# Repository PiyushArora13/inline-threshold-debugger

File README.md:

# inline-threshold-debugger

Non-Intrusive USB-C Inline Diagnostic PCB for Master–Slave Systems

# Overview

This project presents a non-intrusive inline hardware debugger PCB designed for master–slave embedded architectures, where continuous electrical monitoring is required without altering normal system behavior. The board is placed directly in-line between master and slave nodes, enabling real-time observation of voltage and current characteristics while preserving signal integrity.

The design focuses on high-impedance sensing and comparator-based threshold detection, ensuring that monitored signals experience minimal loading and no functional disturbance. This approach allows the debugger to operate transparently within active systems, making it suitable for live diagnostics, validation, and safety monitoring.

A USB Type-C pass-through interface is used for both input and output, providing a compact, reversible, and standardized physical layer compatible with modern embedded and robotics platforms.

# System Architecture

The PCB is built around an Arduino Nano (ATmega328P), which serves as the central processing unit for data acquisition, threshold evaluation, and status indication. The microcontroller samples analog signals via its ADC and coordinates with dedicated comparator stages to classify operating conditions deterministically.

Current sensing is implemented using the ACS712 Hall-effect current sensor, providing galvanically isolated measurement with low insertion impact on the monitored path. This enables accurate current monitoring while maintaining electrical separation and system safety.

Voltage monitoring is achieved through a high-impedance sensing network followed by comparator stages configured with predefined threshold levels. Comparator outputs allow fast detection of limit violations independent of firmware execution latency, ensuring reliable indication under transient conditions.

The inline signal path is designed to maintain impedance continuity between master and slave devices, allowing the debugger PCB to function as a transparent diagnostic layer rather than an active system element.

# Threshold Evaluation and Visual Indication

Measured voltage and current parameters are continuously evaluated against predefined threshold regions. The system provides immediate visual feedback through:

Discrete LEDs indicating individual threshold events

An RGB LED representing overall system state:

Green – Normal / safe operating region

Yellow – Warning or near-limit condition

Red – Critical or unsafe operating condition

This hardware-level indication enables rapid fault identification without requiring external instruments or software-based debugging tools.

# Design Intent and Rationale

Non-intrusive monitoring: High-impedance sensing and isolated current measurement prevent disturbance of the original signal path.

Comparator-based thresholding: Ensures fast, deterministic response independent of microcontroller timing.

Inline architecture: Allows real-time diagnostics in active master–slave systems.

USB Type-C interface: Provides a compact, reversible, and standardized physical connection.

Separation of sensing and indication: Improves robustness and simplifies system-level fault analysis.

# Applications

Inline debugging of master–slave embedded systems

Power and signal integrity validation

Current and voltage health monitoring

Safety threshold enforcement in robotics and control systems

Rapid fault detection during system integration and testing

Project Status

Hardware: Prototype PCB designed and validated

Firmware: Threshold evaluation and visual indication logic implemented

Future work: Data logging, configurable thresholds, and host-side visualization

# Note on File Viewing

KiCad design files are stored in source format and are not rendered by GitHub. Please clone or download the repository and open it in KiCad to view schematics and PCB layouts. Rendered images are included for reference

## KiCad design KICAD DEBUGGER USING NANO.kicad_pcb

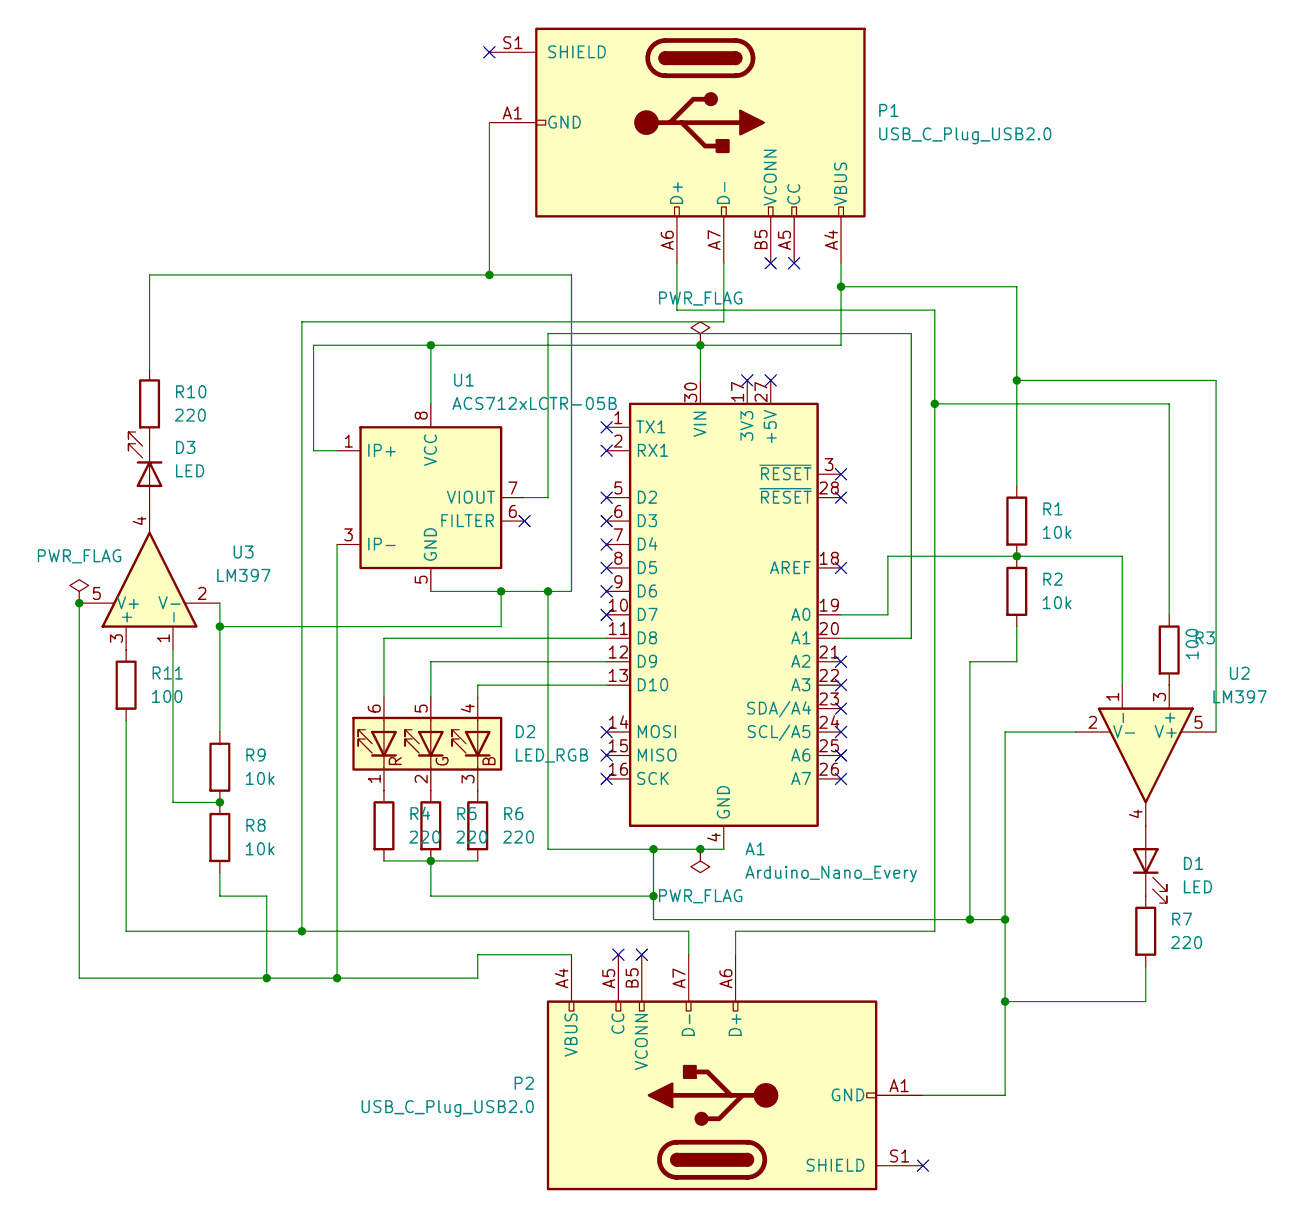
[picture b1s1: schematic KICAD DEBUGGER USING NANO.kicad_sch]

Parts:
A1: Arduino_Nano_Every; Arduino_Nano
D1, D3: LED; LED_0201_0603Metric
D2: LED_RGB; LED_RGB_5050-6
P1, P2: USB_C_Plug_USB2.0; USB_C_Receptacle_GCT_USB4085
R1, R2, R8, R9: 10k; R_2512_6332Metric
R3, R11: 100; R_2512_6332Metric
R4, R5, R6, R7, R10: 220; R_2512_6332Metric
U1: ACS712xLCTR-05B; SOIC-8_3.9x4.9mm_P1.27mm
U2, U3: LM397; SOT-23-5

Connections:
unnamed: A1.19 (A0), R1.2, R2.1, U2.1 (-)
unnamed: A1.20 (A1), U1.7 (VIOUT)
unnamed: A1.11 (D8), D2.6 (RA)
unnamed: A1.12 (D9), D2.5 (GA)
unnamed: A1.13 (D10), D2.4 (BA)
unnamed 5: A1.30 (VIN), P1.A4 (VBUS), P1.A9 (VBUS), P1.B4 (VBUS), P1.B9 (VBUS), R1.1, U1.1 (IP+), U1.2 (IP+), U1.8 (VCC), U2.5 (V+); also elsewhere on the board
unnamed: D1.2 (A), U2.4
unnamed: D1.1 (K), R7.1
unnamed: D2.3 (BK), R6.1
unnamed: D2.2 (GK), R5.1
unnamed: D2.1 (RK), R4.1
unnamed: D3.2 (A), U3.4
unnamed: D3.1 (K), R10.2
unnamed 13: P1.A6 (D+), P2.A6 (D+), R3.1; also elsewhere on the board
unnamed 14: P1.A7 (D-), P2.A7 (D-), R11.2; also elsewhere on the board
unnamed 15: A1.4 (GND), A1.29 (GND), P1.A1 (GND), P1.A12 (GND), P1.B1 (GND), P1.B12 (GND), P2.A1 (GND), P2.A12 (GND), P2.B1 (GND), P2.B12 (GND), R2.2, R4.2, R5.2, R6.2, R7.2, R9.1, R10.1, U1.5 (GND), U2.2 (V-), U3.2 (V-); also elsewhere on the board
unnamed: R3.2, U2.3 (+)
unnamed: R11.1, U3.3 (+)
unnamed: R8.1, R9.2, U3.1 (-)
unnamed 19: P2.A4 (VBUS), P2.A9 (VBUS), P2.B4 (VBUS), P2.B9 (VBUS), R8.2, U1.3 (IP-), U1.4 (IP-), U3.5 (V+); also elsewhere on the board

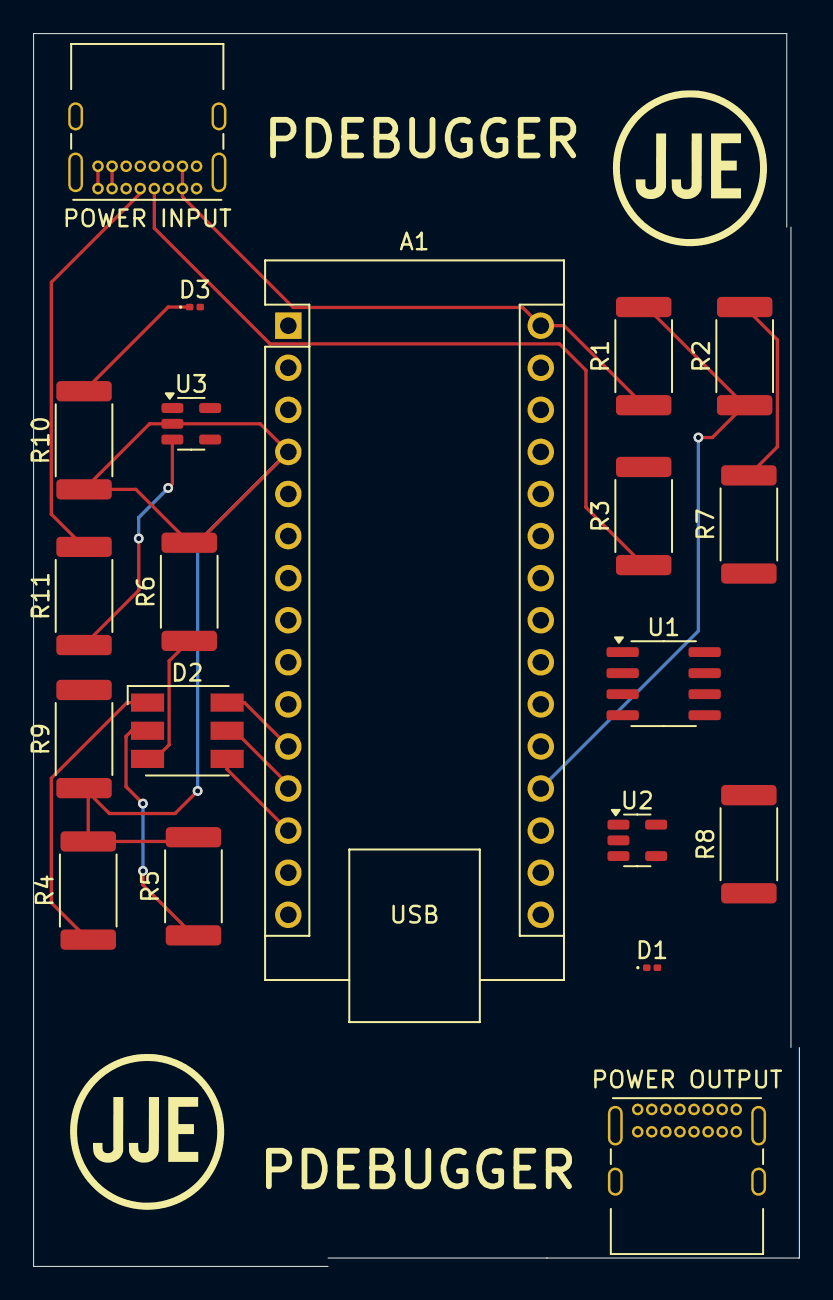
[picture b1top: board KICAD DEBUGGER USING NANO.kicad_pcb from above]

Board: 2 copper layers, 46.2 x 74.4 mm, 20 parts (0 on the bottom side), 20 nets.

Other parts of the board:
POWER INPUT: USB_C_Plug_USB2.0; USB_C_Receptacle_GCT_USB4085
POWER OUTPUT: USB_C_Plug_USB2.0; USB_C_Receptacle_GCT_USB4085

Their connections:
unnamed 5: POWER INPUT.A4 (VBUS), POWER INPUT.A9 (VBUS), POWER INPUT.B4 (VBUS), POWER INPUT.B9 (VBUS); also elsewhere on the board
unnamed 13: POWER INPUT.A6 (D+), POWER OUTPUT.A6 (D+); also elsewhere on the board
unnamed 14: POWER INPUT.A7 (D-), POWER OUTPUT.A7 (D-); also elsewhere on the board
unnamed 15: POWER INPUT.A1 (GND), POWER INPUT.A12 (GND), POWER INPUT.B1 (GND), POWER INPUT.B12 (GND), POWER OUTPUT.A1 (GND), POWER OUTPUT.A12 (GND), POWER OUTPUT.B1 (GND), POWER OUTPUT.B12 (GND); also elsewhere on the board
unnamed 19: POWER OUTPUT.A4 (VBUS), POWER OUTPUT.A9 (VBUS), POWER OUTPUT.B4 (VBUS), POWER OUTPUT.B9 (VBUS); also elsewhere on the board

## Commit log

2026-01-03 Update README with note on KiCad file viewing
    Added note on viewing KiCad design files in README.
2026-01-03 Create Images
